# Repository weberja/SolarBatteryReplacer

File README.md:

# Battery Replacer
The goal of this project is to have a solar powered lithium charger which can replace three AA Batteries in garden lamps.

This started as a project to tinker around with PCBs and have a project with a real goal. In the end i recreated a basically the [Adafruit bq25185 USB / DC / Solar Charger](https://www.adafruit.com/product/6106?srsltid=AfmBOopIVtmkb0ocQaOu4vhrrnbkDsrhC9rcjArDRcQqwAPNf7DQO3vv).

**Key points:**
* Lithium Charger for 4.2V
* MPPT for the poor man - AKA not a full implementation for MPPT but atleast something
* USB Charger
* Replace 3 AA Batteries
* Switch on if it gets dark and run until the battery under voltage protection is triggered

**Voltage & Amps:**
1. 5V á 500 mA Solar panel
2. 5V á 500 mA USB Input
3. 4.2V 500 mA Charging of Lithium Battery
4. 4.2V or lower á 1A Output

## Schematics
Main Component is a BQ25185. It checks all the points. With a 4.2V lithium battery it can also replace the 3 AA Batteries.

One special feature is the use of the LM66200, which is a "Ideal Dual-Diode" which can handle only up to 5.5V. Regarding the planed input and output voltage this device is better then diodes.

To be able to use solar panels with a voltage greater then 5V also two diodes are included. These can be activated with solder jumpers and the LM66200 needs to deactivated with the same solder jumper. See JP5 and JP3.

A different VSET and ISET can be done via the solder jumper JP1 and JP2. The existing resistor needs to be desoldered.

## PCB Design
The design should be as small as possible and have big enough components to tinker around. So it could be smaller but for me it is okay.

"-S+" is the input from the solar cells.
"LED" is the output to the garden LED light. (Voltage of the Battery of of the Input)
To the right of the LED, the Battery connector is provided.

### Front

### Back

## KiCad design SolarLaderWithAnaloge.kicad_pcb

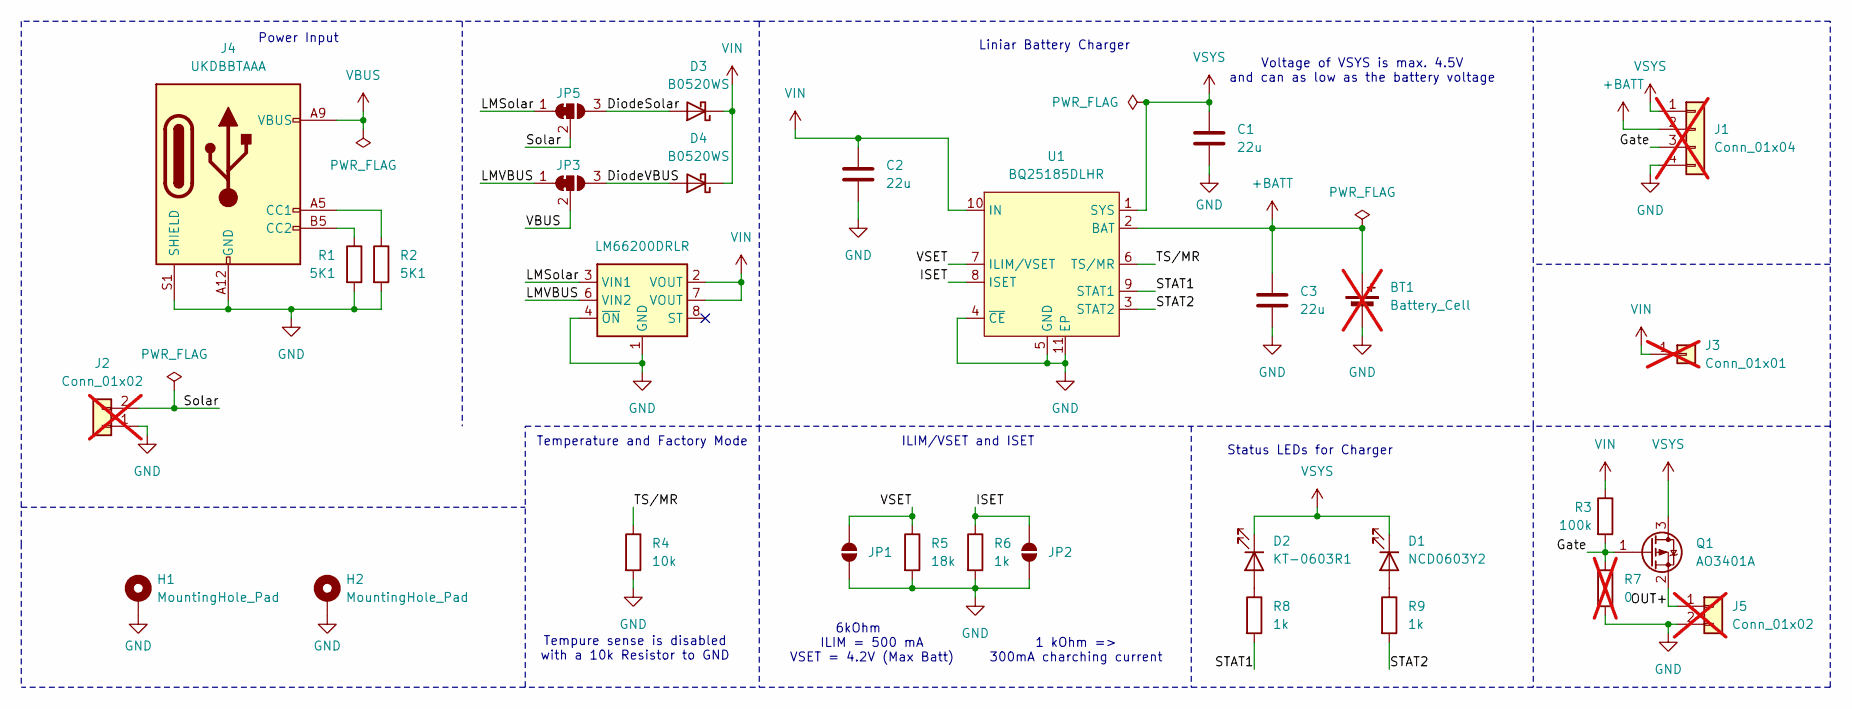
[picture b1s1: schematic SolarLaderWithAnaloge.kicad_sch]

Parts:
BT1: Battery_Cell; JST_PH_S2B-PH-K_1x02_P2.00mm_Horizontal; not fitted
C1, C2, C3: 22u; C_1206_3216Metric
D1: NCD0603Y2; LED_0603_1608Metric
D2: KT-0603R1; LED_0603_1608Metric
D3, D4: B0520WS; D_SOD-123
H1, H2: MountingHole_Pad; MountingHole_2.2mm_M2_DIN965_Pad
J1: Conn_01x04; PinHeader_1x04_P1.00mm_Vertical; not fitted
J2, J5: Conn_01x02; PinHeader_1x02_P2.00mm_Vertical; not fitted
J3: Conn_01x01; PinHeader_1x01_P1.00mm_Vertical; not fitted
J4: UKDBBTAAA; USB_C_Receptacle_HRO_TYPE-C-31-M-17
JP1, JP2: SolderJumper_2_Open; SolderJumper-2_P1.3mm_Open_Pad1.0x1.5mm
JP3, JP5: SolderJumper_3_Bridged12; SolderJumper-3_P1.3mm_Bridged12_Pad1.0x1.5mm
Q1: AO3401A; SOT-23
R1, R2: 5K1; R_0402_1005Metric
R3: 100k; R_0805_2012Metric_Pad1.20x1.40mm_HandSolder
R4: 10k; R_0402_1005Metric
R5: 18k; R_0402_1005Metric
R6: 1k; R_0402_1005Metric
R7: 0; R_0805_2012Metric_Pad1.20x1.40mm_HandSolder; not fitted
R8, R9: 1k; R_0603_1608Metric
U1: BQ25185DLHR; WSON-10_L2.2-W2.0-P0.40-BL-EP_TI_DLH0010A; LCSC Part C19725033
U2: LM66200DRLR; SOT-8 TI

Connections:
+BATT: BT1.1 (+), C3.1, J1.2, U1.2 (BAT)
/DiodeSolar: D3.2 (A), JP5.3 (B)
/DiodeVBUS: D4.2 (A), JP3.3 (B)
/Gate: J1.3, Q1.1 (G), R3.2, R7.1
/ISET: JP2.2 (B), R6.1, U1.8 (ISET)
/LMSolar: JP5.1 (A), U2.3 (VIN1)
/LMVBUS: JP3.1 (A), U2.6 (VIN2)
/OUT+: J5.1, Q1.2 (S)
/STAT1: R8.2, U1.9 (STAT1)
/STAT2: R9.2, U1.3 (STAT2)
/Solar: J2.2, JP5.2 (C)
/TS/MR: R4.1, U1.6 (TS/MR)
/VSET: JP1.2 (B), R5.1, U1.7 (ILIM/VSET)
GND: BT1.2 (-), C1.2, C2.2, C3.2, H1.1, H2.1, J1.4, J2.1, J4.A12 (GND), J4.B12 (GND), J4.S1 (SHIELD), J5.2, JP1.1 (A), JP2.1 (A), R1.2, R2.2, R4.2, R5.2, R6.2, R7.2, U1.4 (~CE), U1.5 (GND), U1.11 (EP), U2.1 (GND), U2.4 (~ON), U2.5 (GND)
unnamed: D1.2 (A), R9.1
unnamed: D2.2 (A), R8.1
unnamed: J4.A5 (CC1), R2.1
unnamed: J4.B5 (CC2), R1.1
VBUS: J4.A9 (VBUS), J4.B9 (VBUS), JP3.2 (C)
VIN: C2.1, D3.1 (K), D4.1 (K), J3.1, R3.1, U1.10 (IN), U2.2 (VOUT), U2.7 (VOUT)
VSYS: C1.1, D1.1 (K), D2.1 (K), J1.1, Q1.3 (D), U1.1 (SYS)

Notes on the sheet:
Status LEDs for Charger
1 kOhm => 300mA charching current
Power Input
ILIM/VSET and ISET
Voltage of VSYS is max. 4.5V and can as low as the battery voltage
Liniar Battery Charger
Temperature and Factory Mode
Tempure sense is disabled with a 10k Resistor to GND
6kOhm ILIM = 500 mA VSET = 4.2V (Max Batt)

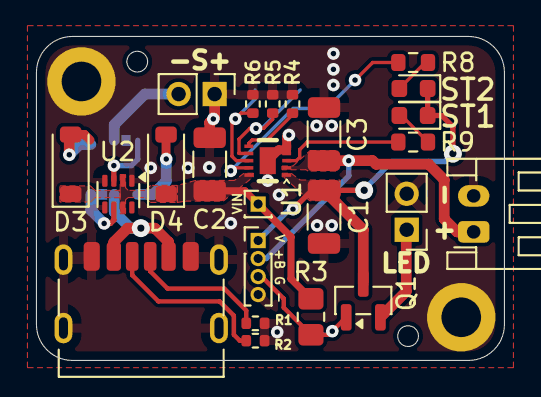
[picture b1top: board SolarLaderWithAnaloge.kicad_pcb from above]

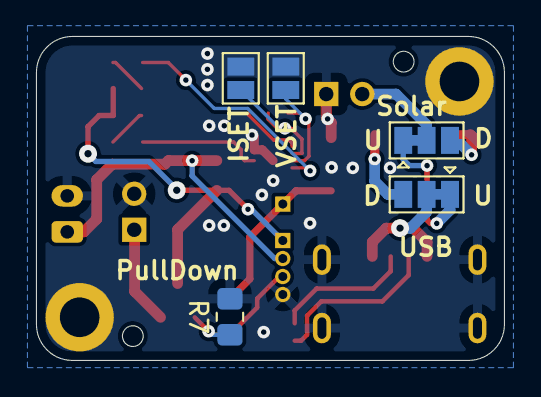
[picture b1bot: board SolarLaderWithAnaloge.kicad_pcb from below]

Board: 2 copper layers, 26.0 x 18.0 mm, 31 parts (5 on the bottom side), 21 nets.

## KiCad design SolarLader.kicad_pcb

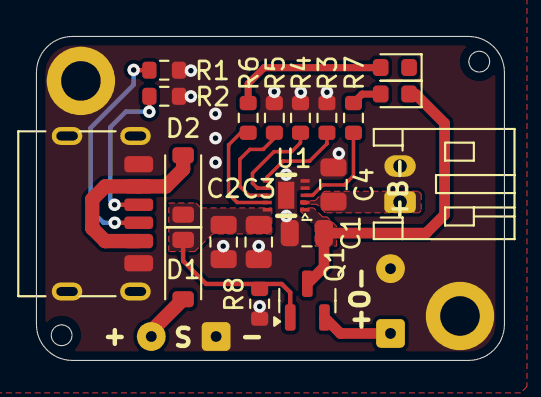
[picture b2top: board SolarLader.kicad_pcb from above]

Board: 2 copper layers, 26.0 x 18.0 mm, 24 parts (0 on the bottom side), 16 nets.

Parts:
BT1: Battery_Cell; JST_PH_S2B-PH-K_1x02_P2.00mm_Horizontal
C1, C2: 10u; C_0805_2012Metric
C3, C4: 1u; C_0805_2012Metric
D1, D2: B5819W SL; D_SOD-123
D3: RED; LED_0603_1608Metric
D4: YELLOW; LED_0603_1608Metric
H3, H4: MountingHole_Pad; MountingHole_2.2mm_M2_DIN965_Pad
J1, J3: Conn_01x02; SolderWire-0.1sqmm_1x02_P3.6mm_D0.4mm_OD1mm
J2: UKDBBTAAA; USB_C_Receptacle_HRO_TYPE-C-31-M-17
Q1: Q_PMOS_GSD; SOT-23
R1, R2: 5K1; R_0603_1608Metric
R3, R6, R7, R8: 10k; R_0603_1608Metric
R4: 5k; R_0603_1608Metric
R5: 1k; R_0603_1608Metric
U1: BQ25185DLHR; WSON-10_L2.2-W2.0-P0.40-BL-EP_TI_DLH0010A

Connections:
+BATT: BT1.1 (+), C4.1, U1.2 (BAT)
/ISET: R5.1, U1.8 (ISET)
/STAT1: R6.2, U1.9 (STAT1)
/STAT2: R7.2, U1.3 (STAT2)
/Solar: D1.2 (A), J1.2
/TS/MR: R3.1, U1.6 (TS/MR)
/VSET: R4.1, U1.7 (ILIM/VSET)
GND: BT1.2 (-), C1.2, C2.2, C3.2, C4.2, H3.1, H4.1, J1.1, J2.A12 (GND), J2.B12 (GND), J2.S1 (SHIELD), J3.2, R1.2, R2.2, R3.2, R4.2, R5.2, R8.2, U1.4 (~CE), U1.5 (GND), U1.11 (EP)
unnamed: D3.2 (A), R6.1
unnamed: D4.2 (A), R7.1
unnamed: J2.A5 (CC1), R2.1
unnamed: J2.B5 (CC2), R1.1
unnamed: J3.1, Q1.2 (S)
VBUS: D2.2 (A), J2.A9 (VBUS), J2.B9 (VBUS)
VIN: C2.1, C3.1, D1.1 (K), D2.1 (K), Q1.1 (G), R8.1, U1.10 (IN)
VSYS: C1.1, D3.1 (K), D4.1 (K), Q1.3 (D), U1.1 (SYS)

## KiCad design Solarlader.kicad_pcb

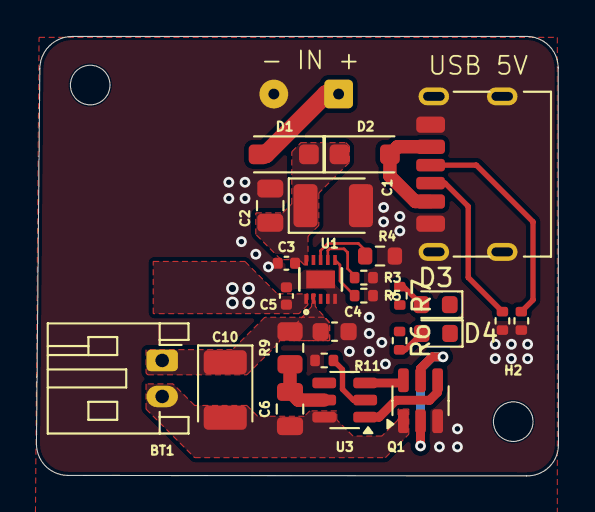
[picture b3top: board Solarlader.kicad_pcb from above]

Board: 4 copper layers, 29.0 x 24.4 mm, 28 parts (0 on the bottom side), 21 nets.

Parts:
BT1: Battery_Cell; JST_PH_S2B-PH-K_1x02_P2.00mm_Horizontal
C1, C10: 100u; CP_EIA-3528-21_Kemet-B
C2: 2.2u 25V; C_0805_2012Metric
C3: 0.1u 25V; C_0402_1005Metric
C4: 1u 35V; C_0603_1608Metric
C5: 10p 10V; C_0402_1005Metric
C6: 100n; C_0805_2012Metric
D1, D2: DSL34; D_SOD-123F
D3: KT-0603W; LED_0603_1608Metric
D4: KT-0603Y2; LED_0603_1608Metric
H1, H2: MountingHole; MountingHole_2.2mm_M2_DIN965
J1: SolderWire-0.1sqmm_1x02_P3.6mm_D0.4mm_OD1mm
J2: UKDBBTAAA; USB_C_Receptacle_HRO_TYPE-C-31-M-17
Q1: HJ8205; SOT-23-6
R1, R2: 5.1k; R_0402_1005Metric
R3: 18k; R_0402_1005Metric
R4: 620; R_0603_1608Metric
R5: 10k; R_0402_1005Metric
R6: 510; R_0402_1005Metric
R7: 300; R_0402_1005Metric
R9: 100; R_0805_2012Metric
R11: 1k; R_0402_1005Metric
U1: BQ25185; WSON10_DLH_TEX-L
U3: DW01A - C686633; SOT-23-6

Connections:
+BATT: BT1.1, C4.1, C10.1, R9.1, U1.2 (BAT)
-BATT: BT1.2, C6.2, C10.2, Q1.1 (S1), U3.6 (GND)
/CS: R11.2, U3.2 (CS)
/ILIM: R3.1, U1.7 (ILIM/VSET)
/ISET: R4.1, U1.8 (ISET)
/STAT1: D3.1 (K), U1.9 (STAT1)
/STAT2: D4.1 (K), U1.3 (STAT2)
/Solar+: D1.2 (A), J1.1
/TS/MR: R5.1, U1.6 (TS/MR)
/VBUS: D2.2 (A), J2.A9 (VBUS), J2.B9 (VBUS)
/VCC: C6.1, R9.2, U3.5 (VCC)
GND: C1.2, C2.2, C3.2, C4.2, C5.2, J1.2, J2.A12 (GND), J2.B12 (GND), J2.S1 (SHIELD), Q1.3 (S2), R1.2, R2.2, R3.2, R4.2, R5.2, R11.1, U1.4 (~CE), U1.5 (GND), U1.11 (EPAD)
unnamed: D3.2 (A), R7.2
unnamed: D4.2 (A), R6.2
unnamed: J2.A5 (CC1), R2.1
unnamed: J2.B5 (CC2), R1.1
unnamed: Q1.2 (D1/D2), Q1.5 (D1/D2)
unnamed: Q1.4 (G1), U3.1 (OD)
unnamed: Q1.6 (G2), U3.3 (OC)
VIN: C1.1, C2.1, C3.1, D1.1 (K), D2.1 (K), U1.10 (IN)
VSYS: C5.1, R6.1, R7.1, U1.1 (SYS)

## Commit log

2025-08-19 init
2025-09-05 Stand mit 1.5V
2025-09-09 Saved between
2025-09-14 REV2 - only 0603 components and mounting hols
2025-10-19 ReleaseCandidate1
2025-12-15 PreRelease 0.1
2025-12-15 added pictures for the readme
2025-12-15 Update the Jumper for the input
